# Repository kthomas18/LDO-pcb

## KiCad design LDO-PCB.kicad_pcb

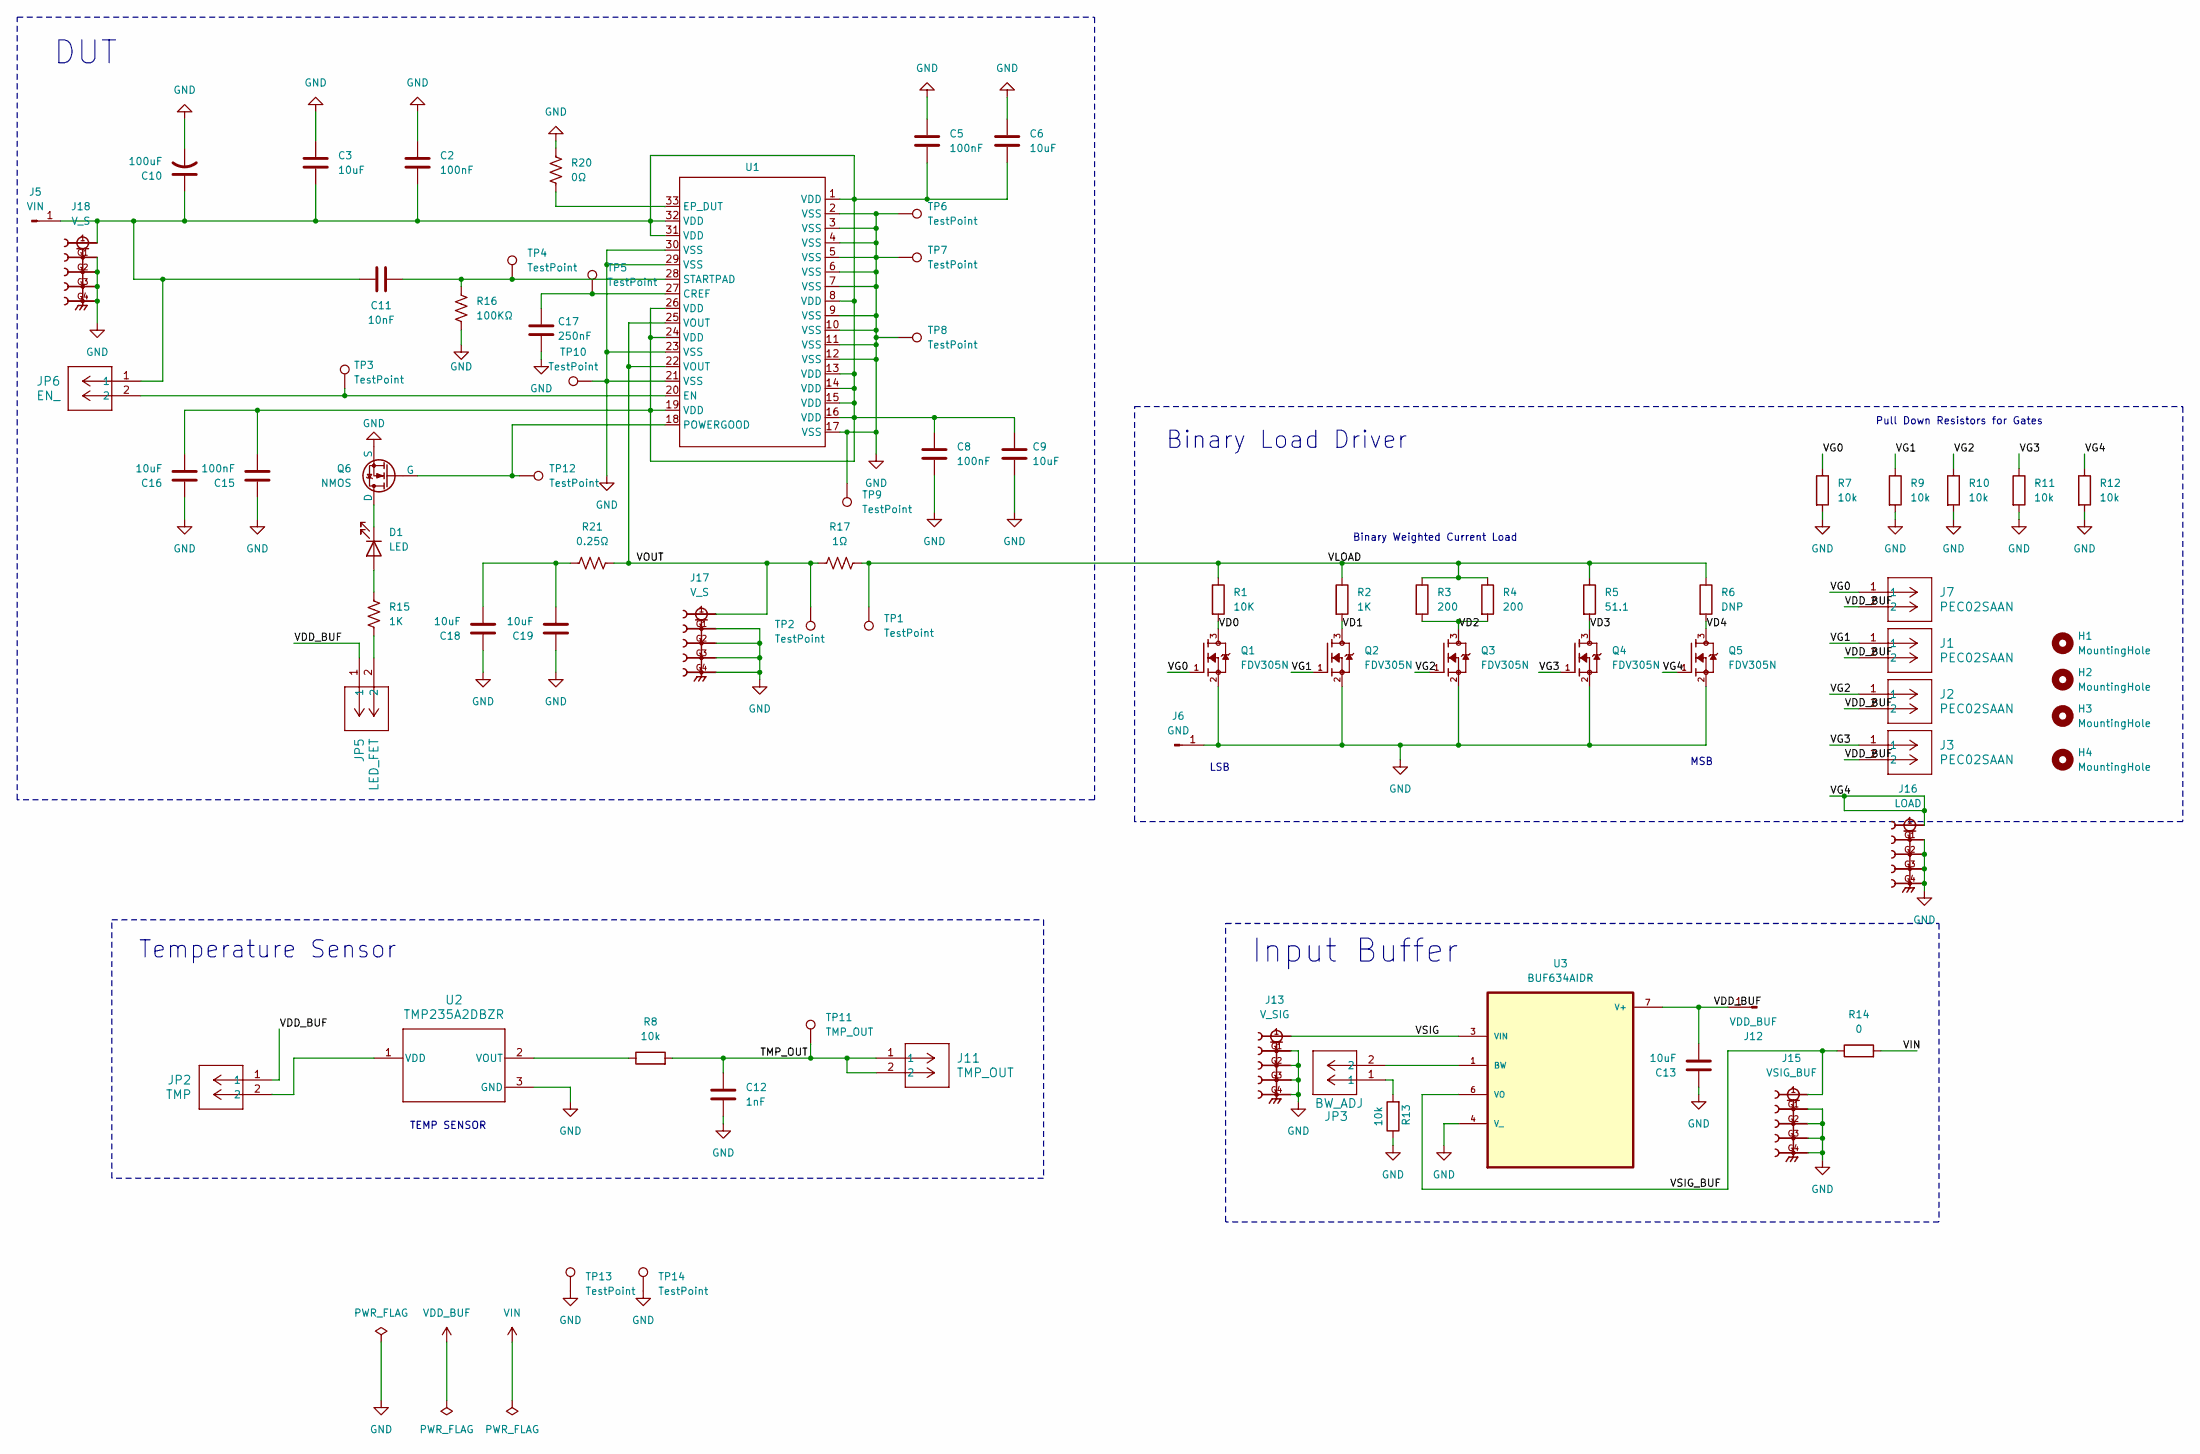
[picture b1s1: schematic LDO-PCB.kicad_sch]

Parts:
C2, C5, C8, C15: 100nF; C_0805_2012Metric_Pad1.18x1.45mm_HandSolder
C3, C6, C9, C16, C18, C19: 10uF; C_0805_2012Metric_Pad1.18x1.45mm_HandSolder
C10: 100uF; CP_Elec_6.3x5.4
C11: 10nF; C_0603_1608Metric_Pad1.08x0.95mm_HandSolder
C12: 1nF; C_0805_2012Metric_Pad1.18x1.45mm_HandSolder; Manufacturer Part Number C0805C102K5RACTU
C13: 10uF; C_0805_2012Metric_Pad1.18x1.45mm_HandSolder; Manufacturer Part Number C0805C106K8RACTU
C17: 250nF; C_0805_2012Metric_Pad1.18x1.45mm_HandSolder
D1: LED; LED_0805_2012Metric
H1, H2, H3, H4: MountingHole; MountingHole_2.5mm
J1, J2, J3, J7: PEC02SAAN; CONN_PxC02S_SUL; Manufacturer Part Number PEC02SAAN
J5: VIN; CALTEST_CT3151-2; Manufacturer Part Number CT3151SP-2
J6: GND; CALTEST_CT3151-2; Manufacturer Part Number CT3151SP-0
J11: TMP_OUT; CONN_PxC02S_SUL; Manufacturer Part Number PEC02SAAN
J12: VDD_BUF; CALTEST_CT3151-2; Manufacturer Part Number CT3151SP-2
J13: V_SIG; SAMTEC_SMA-J-P-H-ST-TH1; Manufacturer Part Number SMA-J-P-H-ST-TH1
J15: VSIG_BUF; SAMTEC_SMA-J-P-H-ST-TH1; Manufacturer Part Number SMA-J-P-H-ST-TH1
J16: LOAD; SAMTEC_SMA-J-P-H-ST-TH1; Manufacturer Part Number SMA-J-P-H-ST-TH1
J17, J18: V_S; SAMTEC_SMA-J-P-H-ST-TH1; Manufacturer Part Number SMA-J-P-H-ST-TH1
JP2: TMP; CONN_PxC02S_SUL; Manufacturer Part Number PEC02SAAN
JP3: BW_ADJ; CONN_PxC02S_SUL; Manufacturer Part Number PEC02SAAN
JP5: LED_FET; CONN_PxC02S_SUL; Manufacturer Part Number PEC02SAAN
JP6: EN_; CONN_PxC02S_SUL; Manufacturer Part Number PEC02SAAN
Q1, Q2, Q3, Q4, Q5: FDV305N; SOT-23; Manufacturer Part Number FDV305N
Q6: NMOS; SOT-523
R1: 10K; R_0805_2012Metric_Pad1.20x1.40mm_HandSolder; Manufacturer Part Number RQ73C2A249RBTD
R2: 1K; R_0805_2012Metric_Pad1.20x1.40mm_HandSolder; Manufacturer Part Number RQ73C2A124RBTD
R3, R4: 200; R_0805_2012Metric_Pad1.20x1.40mm_HandSolder; Manufacturer Part Number RQ73C2A124RBTD
R5: 51.1; R_0805_2012Metric_Pad1.20x1.40mm_HandSolder; Manufacturer Part Number RQ73C2A31R6BTD
R6: DNP; R_0805_2012Metric_Pad1.20x1.40mm_HandSolder; Manufacturer Part Number RQ73C2A15R4BTDF
R7, R8, R9, R10, R11, R12, R13: 10k; R_0805_2012Metric_Pad1.20x1.40mm_HandSolder; Manufacturer Part Number RC0805FR-0710KL
R14: 0; R_0805_2012Metric_Pad1.20x1.40mm_HandSolder; Manufacturer Part Number CRCW08050000Z0EAHP
R15: 1K; R_0805_2012Metric_Pad1.20x1.40mm_HandSolder
R16: 100KΩ; R_0805_2012Metric_Pad1.20x1.40mm_HandSolder
R17: 1Ω; R_1206_3216Metric_Pad1.30x1.75mm_HandSolder
R20: 0Ω; R_0805_2012Metric_Pad1.20x1.40mm_HandSolder
R21: 0.25Ω; R_0805_2012Metric_Pad1.20x1.40mm_HandSolder
TP1, TP2, TP3, TP4, TP5, TP6, TP7, TP8, TP9, TP10, TP12, TP13, TP14: TestPoint; KEYSTONE_5016
TP11: TMP_OUT; KEYSTONE_5016; Manufacturer Part Number 5016
U1: QP-QFN32_7x7_P0.65_EP5.1_EE372
U2: TMP235A2DBZR; DBZ0003A-IPC_A; Manufacturer Part Number TMP235A2DBZR
U3: BUF634AIDR; SOIC127P599X175-8N; Manufacturer Part Number BUF634AIDR

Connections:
/TMP_OUT: C12.1, J11.1, J11.2, R8.2, TP11.1 (1_1)
/VD0: Q1.3, R1.2
/VD1: Q2.3, R2.2
/VD2: Q3.3, R3.2, R4.2
/VD3: Q4.3, R5.2
/VD4: Q5.3, R6.2
/VG0: J7.1, Q1.1, R7.1
/VG1: J1.1, Q2.1, R9.1
/VG2: J2.1, Q3.1, R10.1
/VG3: J3.1, Q4.1, R11.1
/VG4: J16.1, Q5.1, R12.1
/VLOAD: R1.1, R2.1, R3.1, R4.1, R5.1, R6.1, R17.1, TP1.1 (1_1)
/VOUT: J17.1, R17.2, R21.2, TP2.1 (1_1), U1.22 (VOUT), U1.25 (VOUT)
/VSIG: J13.1, U3.3 (VIN)
/VSIG_BUF: J15.1, R14.1, U3.6 (VO)
GND: C2.2, C3.2, C5.1, C6.1, C8.2, C9.2, C10.2, C12.2, C13.1, C15.1, C16.1, C17.2, C18.1, C19.1, J6.1 (Pin_1_1), J13.G1, J13.G2, J13.G3, J13.G4, J15.G1, J15.G2, J15.G3, J15.G4, J16.G1, J16.G2, J16.G3, J16.G4, J17.G1, J17.G2, J17.G3, J17.G4, J18.G1, J18.G2, J18.G3, J18.G4, Q1.2, Q2.2, Q3.2, Q4.2, Q5.2, Q6.3 (S), R7.2, R9.2, R10.2, R11.2, R12.2, R13.1, R16.1, R20.1, TP6.1 (1_1), TP7.1 (1_1), TP8.1 (1_1), TP9.1 (1_1), TP10.1 (1_1), TP13.1 (1_1), TP14.1 (1_1), U1.2 (VSS), U1.3 (VSS), U1.4 (VSS), U1.5 (VSS), U1.6 (VSS), U1.7 (VSS), U1.9 (VSS), U1.10 (VSS), U1.11 (VSS), U1.12 (VSS), U1.17 (VSS), U1.21 (VSS), U1.23 (VSS), U1.29 (VSS), U1.30 (VSS), U2.3 (GND), U3.4 (V_)
unnamed: C18.2, C19.2, R21.1
unnamed: D1.2 (A), R15.1
unnamed: D1.1 (K), Q6.1 (D)
unnamed: C2.1, C3.1, C5.2, C6.2, C8.1, C9.1, C10.1, C11.1, C15.2, C16.2, J5.1 (Pin_1_1), J18.1, JP6.1, U1.1 (VDD), U1.8 (VDD), U1.13 (VDD), U1.14 (VDD), U1.15 (VDD), U1.16 (VDD), U1.19 (VDD), U1.24 (VDD), U1.26 (VDD), U1.31 (VDD), U1.32 (VDD)
unnamed: JP3.1, R13.2
unnamed: JP5.2, R15.2
unnamed: Q6.2 (G), TP12.1 (1_1), U1.18 (POWERGOOD)
unnamed: C17.1, TP5.1 (1_1), U1.27 (CREF)
unnamed: JP6.2, TP3.1 (1_1), U1.20 (EN)
unnamed: R20.2, U1.33 (EP_DUT)
unnamed: C11.2, R16.2, TP4.1 (1_1), U1.28 (STARTPAD)
unnamed: JP2.2, U2.1 (VDD)
unnamed: R8.1, U2.2 (VOUT)
unnamed: JP3.2, U3.1 (BW)
VDD_BUF: C13.2, J1.2, J2.2, J3.2, J7.2, J12.1 (Pin_1_1), JP2.1, JP5.1, U3.7 (V+)
VIN: R14.2

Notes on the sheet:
MSB
Binary Weighted Current Load
LSB
TEMP SENSOR
Pull Down Resistors for Gates
Temperature Sensor
Input Buffer
DUT
Binary Load Driver

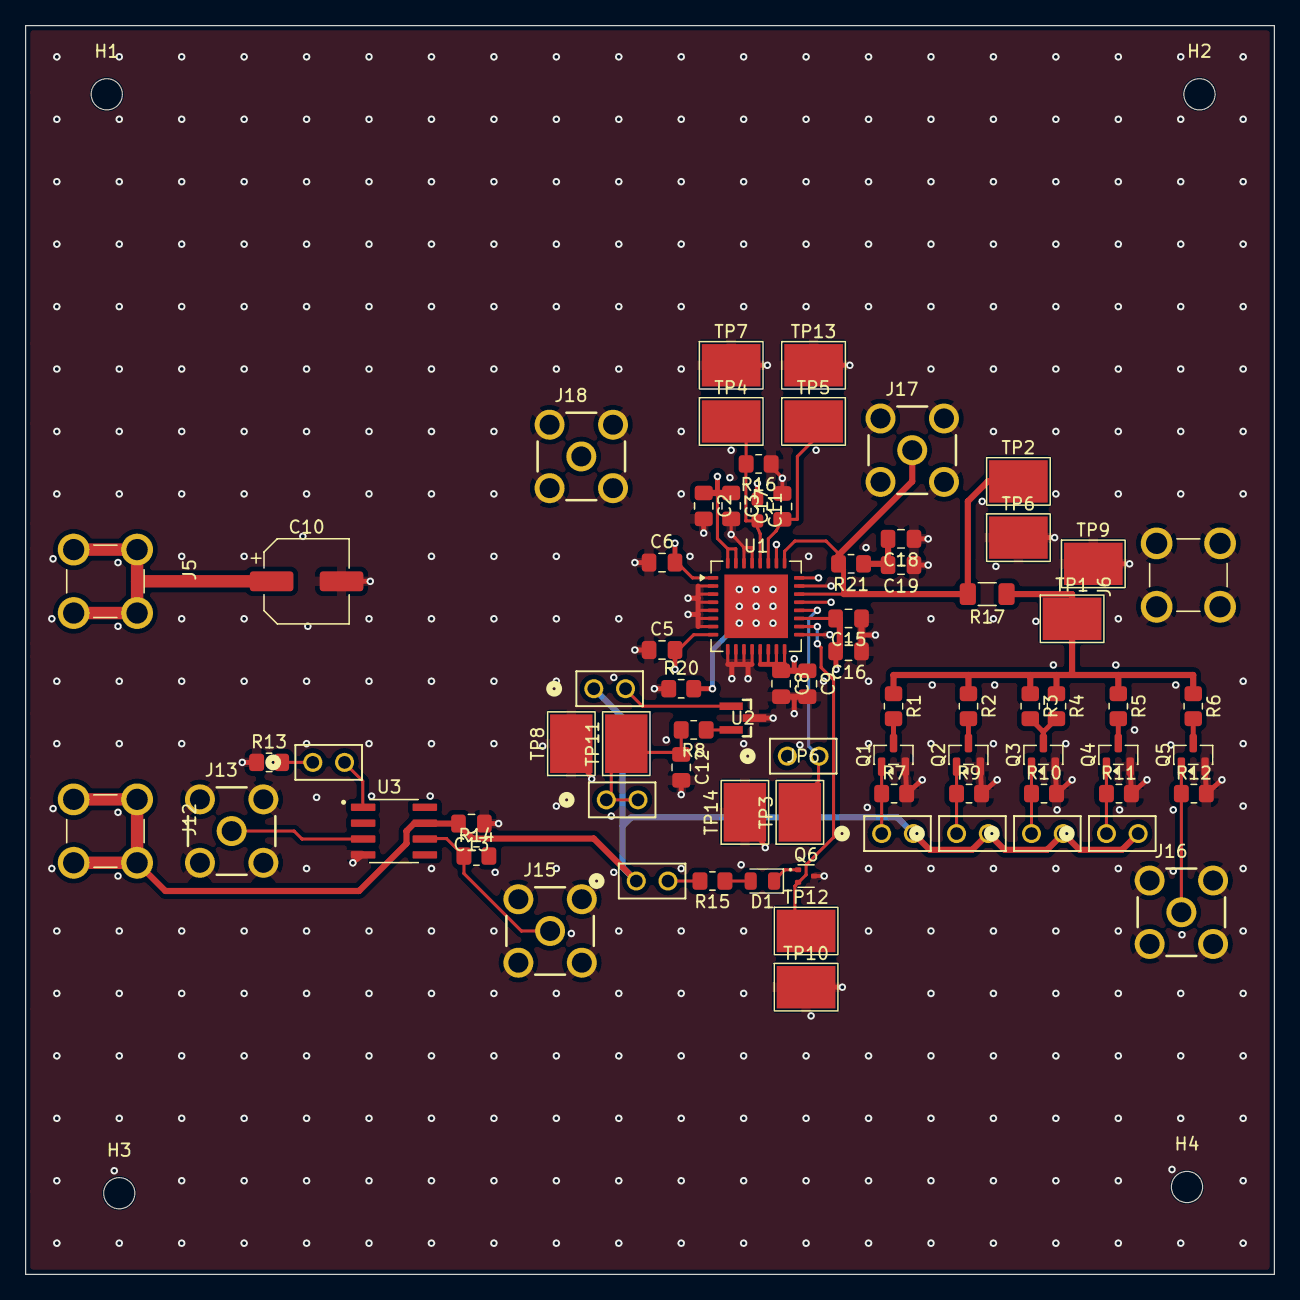
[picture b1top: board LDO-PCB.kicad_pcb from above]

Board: 4 copper layers, 100.0 x 100.0 mm, 79 parts (0 on the bottom side), 31 nets.
